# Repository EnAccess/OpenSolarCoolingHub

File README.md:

<div align="center">

# OpenSolarCoolingHub Documentation Index

## 🛡️ License
This project is open source and licensed as follows:
- **Hardware designs** (PCBs, enclosures): [CERN OHL v2.0 - Strongly Reciprocal](https://gitlab.com/ohwr/project/cernohl/-/wikis/uploads/819d71bea3458f71fba6cf4fb0f2de6b/cern_ohl_s_v2.txt)
- **Firmware / Software**: [MIT License](https://opensource.org/license/mit/)
- **Documentation**: [Creative Commons Attribution 4.0 International (CC BY 4.0)](https://creativecommons.org/licenses/by/4.0/)
- See the full [LICENSE](./LICENSE) file for full details.
<br>

**Solar Powered IoT Cooling Hubs**  
_This is a project that brings together architecture, electronics, Internet of Things (IoT), and solar engineering to create affordable and sustainable cooling systems specifically designed for off-grid communities. By integrating smart design with energy-efficient technology and renewable energy sources, the project aims to provide reliable cooling solutions where access to electricity is limited or unavailable. The goal is to improve quality of life, reduce post-harvest losses, and support health and food storage needs in remote or underserved areas._

## 🔗 Cold Room Exterior
This image shows the exterior design of the solar-powered cold room, constructed with durable, insulated materials to maintain optimal internal temperatures. The structure is optimized for energy efficiency and environmental resilience, making it ideal for use in rural or off-grid locations. Its compact and modular design allows for easy transport, installation, and maintenance in remote areas.

## 🔗 IOT Sytem PCB
Displayed here is the custom-designed Printed Circuit Board (PCB) for the IoT system. This board forms the core of the system’s electronics, managing sensor data, control signals, and wireless communication. The PCB is engineered to interface with temperature, humidity, and door sensors, and is optimized for low power consumption and real-time data transmission, supporting remote monitoring and control via a web dashboard.

---

## 🔗 Live IoT Dashboard  
The live IoT dashboard provides real-time monitoring of environmental conditions inside the cold room. It displays key metrics such as temperature, humidity, and system status, allowing users to remotely track and manage performance. The intuitive interface makes it easy for operators to respond to alerts and optimize energy use, ensuring food and medical supplies remain safely stored.

👉 [View Real-time Sensor Display](http://solarcoolingproject.atwebpages.com/RealtimeDisplayImproved.php)

---

<br><br><br><br>

## 📂 Folder-wise Documentation Overview
<br>

## 🧊 1. Cold Room Design 
A comprehensive architectural and systems layout for the off-grid cold room solution. Designed using SolidWorks and Archicad, this section includes construction drawings, 3D models, conceptual diagrams, and thermal/digital integration details.

🔗 Archicad Files - [Link](https://github.com/EnAccess/OpenSolarCoolingHub/tree/b22f68ab80e7eb956e8c33c35e9078b9c4da2ed1/Cold%20Room%20Design/ColdRoom/Archicad%20Files) : Contains the primary architectural plan (FarmFreeze_Munakyalo (ArchiCAD 25).pln) with accompanying documentation.

🔗 CAD Exports - [Link](https://github.com/EnAccess/OpenSolarCoolingHub/tree/b22f68ab80e7eb956e8c33c35e9078b9c4da2ed1/Cold%20Room%20Design/ColdRoom/CAD%20Exports) : Includes PDFs and images of the VIP latrine, tank and base, gate, fence, and full site layout.

🔗 Diagrams - [Link](https://github.com/EnAccess/OpenSolarCoolingHub/tree/b22f68ab80e7eb956e8c33c35e9078b9c4da2ed1/Cold%20Room%20Design/ColdRoom/Diagrams) : Contains structural and conceptual system diagrams.

🔗 System Architecture - [Link](https://github.com/EnAccess/OpenSolarCoolingHub/tree/b22f68ab80e7eb956e8c33c35e9078b9c4da2ed1/Cold%20Room%20Design/SystemArchitecture) : Describes the thermal, electrical, and digital system integration to support off-grid functionality.<br><br>

## 📎 2. Component Datasheets
This folder contains the technical specifications of all key components used across the system. Includes datasheets for sensors (DHT22, MLX90614), power modules, GSM, and Arduino boards. - [Link](https://github.com/EnAccess/OpenSolarCoolingHub/tree/b22f68ab80e7eb956e8c33c35e9078b9c4da2ed1/Component%20Datasheets) 

🔗 readme - [Link](https://github.com/EnAccess/OpenSolarCoolingHub/tree/edee4dc87492873370343514b17ce90f6df560b8/Component%20Datasheets) : Lists and explains each hardware module with links to PDFs.<br><br>

## 💰 3. Financial Model Templates
An Excel-based financial modeling toolkit for evaluating the Pay-as-You-Store pricing strategy and sustainability metrics.
 - [Link](https://github.com/EnAccess/OpenSolarCoolingHub/tree/b22f68ab80e7eb956e8c33c35e9078b9c4da2ed1/Financial%20Model%20Templates) 
🔗 readme.md - [Link](https://github.com/EnAccess/OpenSolarCoolingHub/blob/b22f68ab80e7eb956e8c33c35e9078b9c4da2ed1/Financial%20Model%20Templates/readme.md) : Overview of model usage.

📊 Includes:

Pay_as_You_Store_Financial_Model.xlsx - [Link](https://github.com/EnAccess/OpenSolarCoolingHub/blob/b22f68ab80e7eb956e8c33c35e9078b9c4da2ed1/Financial%20Model%20Templates/Pay_as_You_Store_Financial_Model.xlsx) 

User_Guide_Pay_as_You_Store_Model.pdf - [Link](https://github.com/EnAccess/OpenSolarCoolingHub/blob/b22f68ab80e7eb956e8c33c35e9078b9c4da2ed1/Financial%20Model%20Templates/User_Guide_Pay_as_You_Store_Model.pdf) <br><br>

## 🧠 4. IoT Firmware
Embedded C/C++ code written and compiled using Arduino IDE, designed for the Arduino Mega. This firmware handles sensor input, GSM communication, and relay control logic.

🔗 libraries - [Link](https://github.com/EnAccess/OpenSolarCoolingHub/tree/b22f68ab80e7eb956e8c33c35e9078b9c4da2ed1/IOT%20System%20Arduino%20Firmware/libraries) : Required libraries like DHTlib and Adafruit MLX90614.

🔗 src - [Link](https://github.com/EnAccess/OpenSolarCoolingHub/tree/b22f68ab80e7eb956e8c33c35e9078b9c4da2ed1/IOT%20System%20Arduino%20Firmware/src) : Source code examples including merged sensor tests, GSM modules, relay switching, and address configuration.

🔗 README.md - [Link](https://github.com/EnAccess/OpenSolarCoolingHub/blob/243c3de1c4182eb7e5c24f7d1faaf12b4d0801e8/IOT%20System%20Arduino%20Firmware/README.md) : Firmware overview and setup guide.<br><br>

## 🧱 5. IoT System Enclosure
Designed in OpenSCAD, this section provides both editable 3D models and printable STL files for creating protective enclosures for the PCB.

🔗 3D Models - [Link](https://github.com/EnAccess/OpenSolarCoolingHub/tree/b22f68ab80e7eb956e8c33c35e9078b9c4da2ed1/IOT%20System%20Enclosure/3D%20Models) : .step files for customization and mechanical fitting.

🔗 STL Files - [Link](https://github.com/EnAccess/OpenSolarCoolingHub/tree/b22f68ab80e7eb956e8c33c35e9078b9c4da2ed1/IOT%20System%20Enclosure/STL%20Files) : Ready-to-print STL files for 3D printing.<br><br>

## 💻 6. IoT PCB Design
PCB schematics, layout, and manufacturing-ready files created using CircuitMaker (Altium's free tool). Includes Gerbers, BoMs, pick-and-place files, and fabrication data. - [Link](https://github.com/EnAccess/OpenSolarCoolingHub/tree/b22f68ab80e7eb956e8c33c35e9078b9c4da2ed1/IOT%20System%20PCB) 

🔗 Export Files - [Link](https://github.com/EnAccess/OpenSolarCoolingHub/tree/b22f68ab80e7eb956e8c33c35e9078b9c4da2ed1/IOT%20System%20PCB/Export%20FIles) : Contains all files for fabrication, drilling, and assembly.

🔗 schematics - [Link](https://github.com/EnAccess/OpenSolarCoolingHub/tree/b22f68ab80e7eb956e8c33c35e9078b9c4da2ed1/IOT%20System%20PCB/schematics) : Design files including SchDoc, CMPcbDoc, and the project structure.<br><br>

## 🧪 7. IoT Simulation
Logic simulation and virtual validation of the IoT system using Proteus Professional. - [Link](https://github.com/EnAccess/OpenSolarCoolingHub/tree/2582ba2290185b933453911665ca5a5f1b0d1c63/IOT%20System%20Simulation%20with%20Proteus%20Pro) 

🔗 readmefile.md - [Link](https://github.com/EnAccess/OpenSolarCoolingHub/blob/2582ba2290185b933453911665ca5a5f1b0d1c63/IOT%20System%20Simulation%20with%20Proteus%20Pro/readmefile.md) : Instructions and configuration.

Includes:

Cold Solar Storage Proteus Simulation.pdsprj<br><br>

## 🌐 8. IoT System Website
Built with PHP, MySQL, HTML, CSS, the cloud dashboard enables real-time monitoring of cold room conditions remotely.

🔗 public - [Link](https://github.com/EnAccess/OpenSolarCoolingHub/tree/2582ba2290185b933453911665ca5a5f1b0d1c63/IOT%20System%20Website/public) : All PHP scripts for inserting, fetching, and displaying sensor data.<br><br>
🔗 readmefile.md - [Link](https://github.com/EnAccess/OpenSolarCoolingHub/blob/2582ba2290185b933453911665ca5a5f1b0d1c63/IOT%20System%20Website/README.md)

## 🎥 9. Project Images and Videos
A visual gallery showing the project progress and deliverables including 3D PCB renderings and schematics.
 - [Link](https://github.com/EnAccess/OpenSolarCoolingHub/tree/2582ba2290185b933453911665ca5a5f1b0d1c63/Project%20Images%20and%20Videos) 

Includes: PCB 2D.PNG, PCB 3D ANGLE.PNG, Schematic.PNG, etc.<br><br>

## 🧪 10. System Testing
This section documents the calibration, test planning, and final performance results of the overall system.

🔗 Calibration - [Link](https://github.com/EnAccess/OpenSolarCoolingHub/tree/2582ba2290185b933453911665ca5a5f1b0d1c63/System%20Testing/Calibration) : Logs and notes on sensor tuning.

🔗 TestPlans - [Link](https://github.com/EnAccess/OpenSolarCoolingHub/tree/2582ba2290185b933453911665ca5a5f1b0d1c63/System%20Testing/TestPlans) : Structured validation plans.

🔗 TestResults - [Link](https://github.com/EnAccess/OpenSolarCoolingHub/tree/2582ba2290185b933453911665ca5a5f1b0d1c63/System%20Testing/TestResults) : Performance outcomes and notes.<br><br>

## 📚 11. Technical References
Academic and industry references used for component selection, system design, and technical justification.
 - [Link](https://github.com/EnAccess/OpenSolarCoolingHub/tree/2582ba2290185b933453911665ca5a5f1b0d1c63/Technical%20References) 
<br><br>

## 📘 12. User Manual
End-user guide for setup, usage, and maintenance of the cold room system.
 - [Link](https://github.com/EnAccess/OpenSolarCoolingHub/tree/2582ba2290185b933453911665ca5a5f1b0d1c63/User%20Manual) 
🔗 readme.md - [Link](https://github.com/EnAccess/OpenSolarCoolingHub/blob/2582ba2290185b933453911665ca5a5f1b0d1c63/User%20Manual/readme.md) : Step-by-step instructions for installation and safe use. <br><br>

---

</div>

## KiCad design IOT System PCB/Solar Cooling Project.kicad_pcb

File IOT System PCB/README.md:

# IoT System PCB – Open Solar Cooling Hub using KiCAD

This repository contains the PCB design files for the IoT Monitoring System used in the Open Solar Cooling Hub, created and managed using **KiCAD**. The project includes schematics, PCB layout, fabrication files (Gerbers, drill files), assembly files (BOM, Pick & Place), and a 3D model for enclosure design. This guide explains how to open, modify, and produce the PCB using KiCAD.

---

## Prerequisites

1. **Install KiCAD**:
   - Download KiCAD 9.0.3 from [kicad.org](https://www.kicad.org/download/) for Windows, macOS, or Linux.
   - Install and launch KiCAD.
  
   - Application: KiCad x64 on x64

   - Libraries:
     	- wxWidgets 3.2.8
      - FreeType 2.13.3
      - HarfBuzz 10.2.0
      - FontConfig 2.15.0
      - libcurl/8.13.0-DEV Schannel zlib/1.3.1

2. **Required Files**:
   - `Solar Cooling Project.kicad_pro`: KiCAD project file.
   - `Solar Cooling Project.kicad_sch`: Schematic file.
   - `Solar Cooling Project.kicad_pcb`: PCB layout file.
   - Reference files :
     - Gerber files (`Solar Cooling Project-F_Cu.gbr`, `B_Cu.gbr`, etc.)
     - Drill files (`Solar Cooling Project-PTH.drl`, `NPTH.drl`)
     - BOM (`BOM_PartType-Open Solar Cooling Hub PCB Project.xlsx`)
     - Pick & Place (`Pick Place for IOT B oard FIle.txt`)
     - Assembly PDF (`Assembly.PDF`)
     - 3D model (`IOT B oard FIle.step`)

---

## Folder Structure and Content Description

The project follows standard hardware development practices, with files organized for PCB fabrication, assembly, and modification.

| Folder/File | Purpose |
|-------------|---------|
| `Gerber/` | PCB fabrication layers (copper, soldermask, silkscreen, etc.) |
| `NC Drill/` | Drill files for PTH and NPTH holes |
| `PCBA/` | Assembly files (BOM, Pick & Place, Assembly PDF) |
| `ExportSTEP/` | 3D STEP model for enclosure design |
| `Solar Cooling Project.kicad_pro` | KiCAD project file |
| `Solar Cooling Project.kicad_sch` | Schematic file |
| `Solar Cooling Project.kicad_pcb` | PCB layout file |
| `README.md` | Project documentation |

---

## How to Open and Modify the PCB Design in KiCAD

### 1. Open the Project
1. Launch KiCAD and open `Solar Cooling Project.kicad_pro` in the project manager.
2. This loads the schematic (`Solar Cooling Project.kicad_sch`) and PCB layout (`Solar Cooling Project.kicad_pcb`).

### 2. Edit the Schematic
1. Open the schematic editor (Eeschema) by clicking the schematic icon in the project manager.
2. Verify components, connections, and net labels against the original BOM and schematic reference .
3. **Modify **:
   - Add/remove components using KiCAD’s symbol libraries or create custom symbols.
   - Update net labels for clarity.
   - Assign footprints to each symbol via the “Assign Footprints” tool, ensuring compatibility with the BOM and Pick & Place file.
4. Generate a netlist (File > Export > Netlist) for PCB layout.

### 3. Edit the PCB Layout
1. Open the PCB editor (Pcbnew) by clicking the PCB icon in the project manager.
2. Import the netlist (File > Import > Netlist) to populate components.
3. **Validate Layout**:
   - Compare the board outline with `Solar Cooling Project-Edge_Cuts.gbr`.
   - Verify component placements using `Pick Place for IOT B oard FIle.txt` (import via File > Import > Placement File).
   - Check routing against Gerber files (`F_Cu.gbr`, `B_Cu.gbr`) using KiCAD’s Gerber Viewer (File > Import > Gerber Files).
4. **Modify (if needed)**:
   - Adjust component positions in Pcbnew.
   - Reroute traces to optimize the layout.
   - Update the board outline on the `Edge.Cuts` layer.
5. **Import Drill Files**:
   - Import `Solar Cooling Project-PTH.drl` and `NPTH.drl` (File > Import > Drill Files) to ensure correct via and hole placement.
6. **3D Verification**:
   - View the PCB in 3D (View > 3D Viewer) and compare with `IOT B oard FIle.step`.
   - Assign 3D models to footprints if needed (Footprint Properties > 3D Settings).

### 4. Generate Fabrication and Assembly Files
1. **Gerber Files**:
   - In Pcbnew, go to File > Plot.
   - Select layers: `F.Cu`, `B.Cu`, `F.Silkscreen`, `B.Silkscreen`, `F.Mask`, `B.Mask`, `Edge.Cuts`.
   - Output to a `Gerber/` folder.
   - Verify against original Gerbers using a Gerber viewer (e.g., KiCAD’s Gerber Viewer or Gerbv).
2. **Drill Files**:
   - In Pcbnew, go to File > Fabrication Outputs > Drill Files.
   - Generate Excellon drill files for PTH and NPTH.
   - Output to a `NC Drill/` folder.
3. **Bill of Materials (BOM)**:
   - In Eeschema, go to Tools > Generate Bill of Materials.
   - Export as CSV or XLSX to `PCBA/BOM.xlsx`.
   - Cross-check with `BOM_PartType-Open Solar Cooling Hub PCB Project.xlsx`.
4. **Pick & Place File**:
   - In Pcbnew, go to File > Fabrication Outputs > Component Placement File.
   - Output to `PCBA/Pick_Place.txt`.
   - Verify against `Pick Place for IOT B oard FIle.txt`.
5. **Assembly Drawing**:
   - In Pcbnew, go to File > Plot and export a PDF of the board layout to `PCBA/Assembly.pdf`.
6. **3D Model**:
   - In Pcbnew, go to File > Export > STEP.
   - Save to `ExportSTEP/Solar_Cooling_Project.step`.

### 5. Validate Outputs
- **Gerber Comparison**: Use a Gerber viewer to ensure KiCAD-generated Gerbers match the original Gerbers.
- **BOM and Pick & Place**: Confirm component lists and placements align with the original files.
- **Fabrication Test**: Send Gerber and drill files to a PCB manufacturer (e.g., JLCPCB) to verify acceptance.
- **Assembly Check**: Provide BOM, Pick & Place, and Assembly PDF to an SMT service for validation.

---

## How to Use the Outputs

- **Fabrication**: Send the `Gerber/` and `NC Drill/` folders to a PCB manufacturer e.g., JLCPCB, PCBWay.
- **Assembly**: Provide `PCBA/BOM.xlsx`, `PCBA/Pick_Place.txt`, and `PCBA/Assembly.pdf` to an SMT assembly service.
- **Modify/Rebuild**: Use `Solar Cooling Project.kicad_sch` and `.kicad_pcb` in KiCAD to edit the design and regenerate outputs.
- **Enclosure Design**: Use `ExportSTEP/Solar_Cooling_Project.step` in CAD tools like OpenSCAD or FreeCAD.

---

## Licensing

This project is licensed under the **CERN Open Hardware License v2.0**. Ensure all modifications and derivatives retain this license.

---

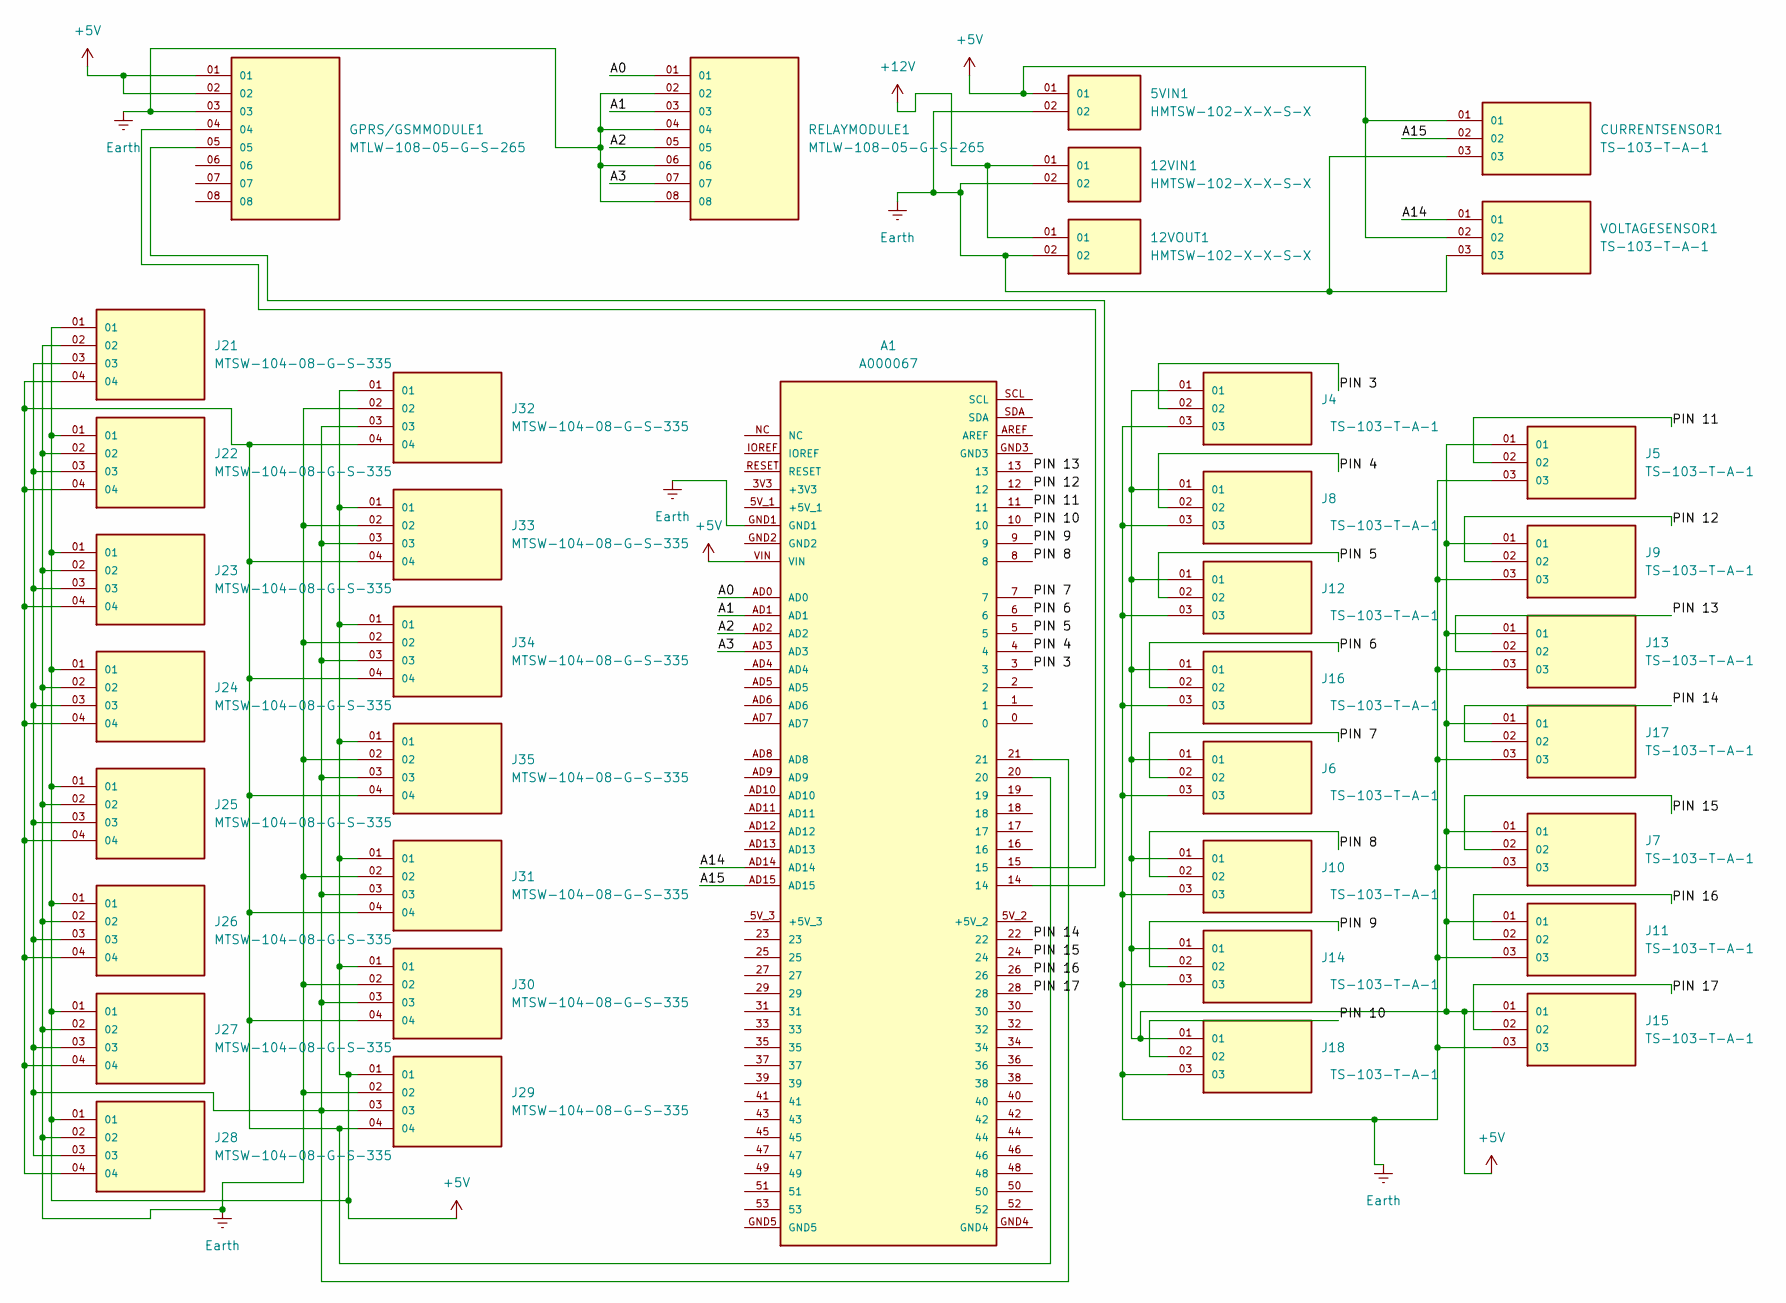
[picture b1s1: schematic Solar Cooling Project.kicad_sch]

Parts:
5VIN1, 12VIN1, 12VOUT1: HMTSW-102-X-X-S-X; SAMTEC_HMTSW-102-X-X-S-X; PARTREV A
A1: A000067; MODULE_A000067; PARTREV 3
CURRENTSENSOR1: TS-103-T-A-1; SAMTEC_TS-103-T-A-1; PARTREV R
GPRS/GSMMODULE1: MTLW-108-05-G-S-265; SAMTEC_MTLW-108-05-G-S-265; PARTREV R
J4, J5, J6, J7, J8, J9, J10, J11, J12, J13, J14, J15, J16, J17, J18: TS-103-T-A-1; SAMTEC_TS-103-T-A-1; PARTREV R
J21, J22, J23, J24, J25, J26, J27, J28, J29, J30, J31, J32, J33, J34, J35: MTSW-104-08-G-S-335; SAMTEC_MTSW-104-08-G-S-335; PARTREV R
RELAYMODULE1: MTLW-108-05-G-S-265; SAMTEC_MTLW-108-05-G-S-265; PARTREV R
VOLTAGESENSOR1: TS-103-T-A-1; SAMTEC_TS-103-T-A-1; PARTREV R

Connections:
+5V: 5VIN1.01, A1.VIN, CURRENTSENSOR1.01, GPRS/GSMMODULE1.01, GPRS/GSMMODULE1.02, J4.01, J5.01, J6.01, J7.01, J8.01, J9.01, J10.01, J11.01, J12.01, J13.01, J14.01, J15.01, J16.01, J17.01, J18.01, J21.01, J22.01, J23.01, J24.01, J25.01, J26.01, J27.01, J28.01, J29.01, J30.01, J31.01, J32.01, J33.01, J34.01, J35.01, VOLTAGESENSOR1.02
+12V: 12VIN1.01, 12VOUT1.01
/A0: A1.AD0, RELAYMODULE1.01
/A1: A1.AD1, RELAYMODULE1.03
/A2: A1.AD2, RELAYMODULE1.05
/A3: A1.AD3, RELAYMODULE1.07
/A14: A1.AD14, VOLTAGESENSOR1.01
/A15: A1.AD15, CURRENTSENSOR1.02
/PIN 3: A1.3, J4.02
/PIN 4: A1.4, J8.02
/PIN 5: A1.5, J12.02
/PIN 6: A1.6, J16.02
/PIN 7: A1.7, J6.02
/PIN 8: A1.8, J10.02
/PIN 9: A1.9, J14.02
/PIN 10: A1.10, J18.02
/PIN 11: A1.11, J5.02
/PIN 12: A1.12, J9.02
/PIN 13: A1.13, J13.02
/PIN 14: A1.22, J17.02
/PIN 15: A1.24, J7.02
/PIN 16: A1.26, J11.02
/PIN 17: A1.28, J15.02
Earth: 5VIN1.02, 12VIN1.02, 12VOUT1.02, A1.GND1, CURRENTSENSOR1.03, GPRS/GSMMODULE1.03, J4.03, J5.03, J6.03, J7.03, J8.03, J9.03, J10.03, J11.03, J12.03, J13.03, J14.03, J15.03, J16.03, J17.03, J18.03, J21.02, J22.02, J23.02, J24.02, J25.02, J26.02, J27.02, J28.02, J29.02, J30.02, J31.02, J32.02, J33.02, J34.02, J35.02, RELAYMODULE1.02, RELAYMODULE1.04, RELAYMODULE1.06, RELAYMODULE1.08, VOLTAGESENSOR1.03
unnamed: A1.14, GPRS/GSMMODULE1.05
unnamed: A1.15, GPRS/GSMMODULE1.04
unnamed: A1.20, J21.04, J22.04, J23.04, J24.04, J25.04, J26.04, J27.04, J28.04, J29.04, J30.04, J31.04, J32.04, J33.04, J34.04, J35.04
unnamed: A1.21, J21.03, J22.03, J23.03, J24.03, J25.03, J26.03, J27.03, J28.03, J29.03, J30.03, J31.03, J32.03, J33.03, J34.03, J35.03

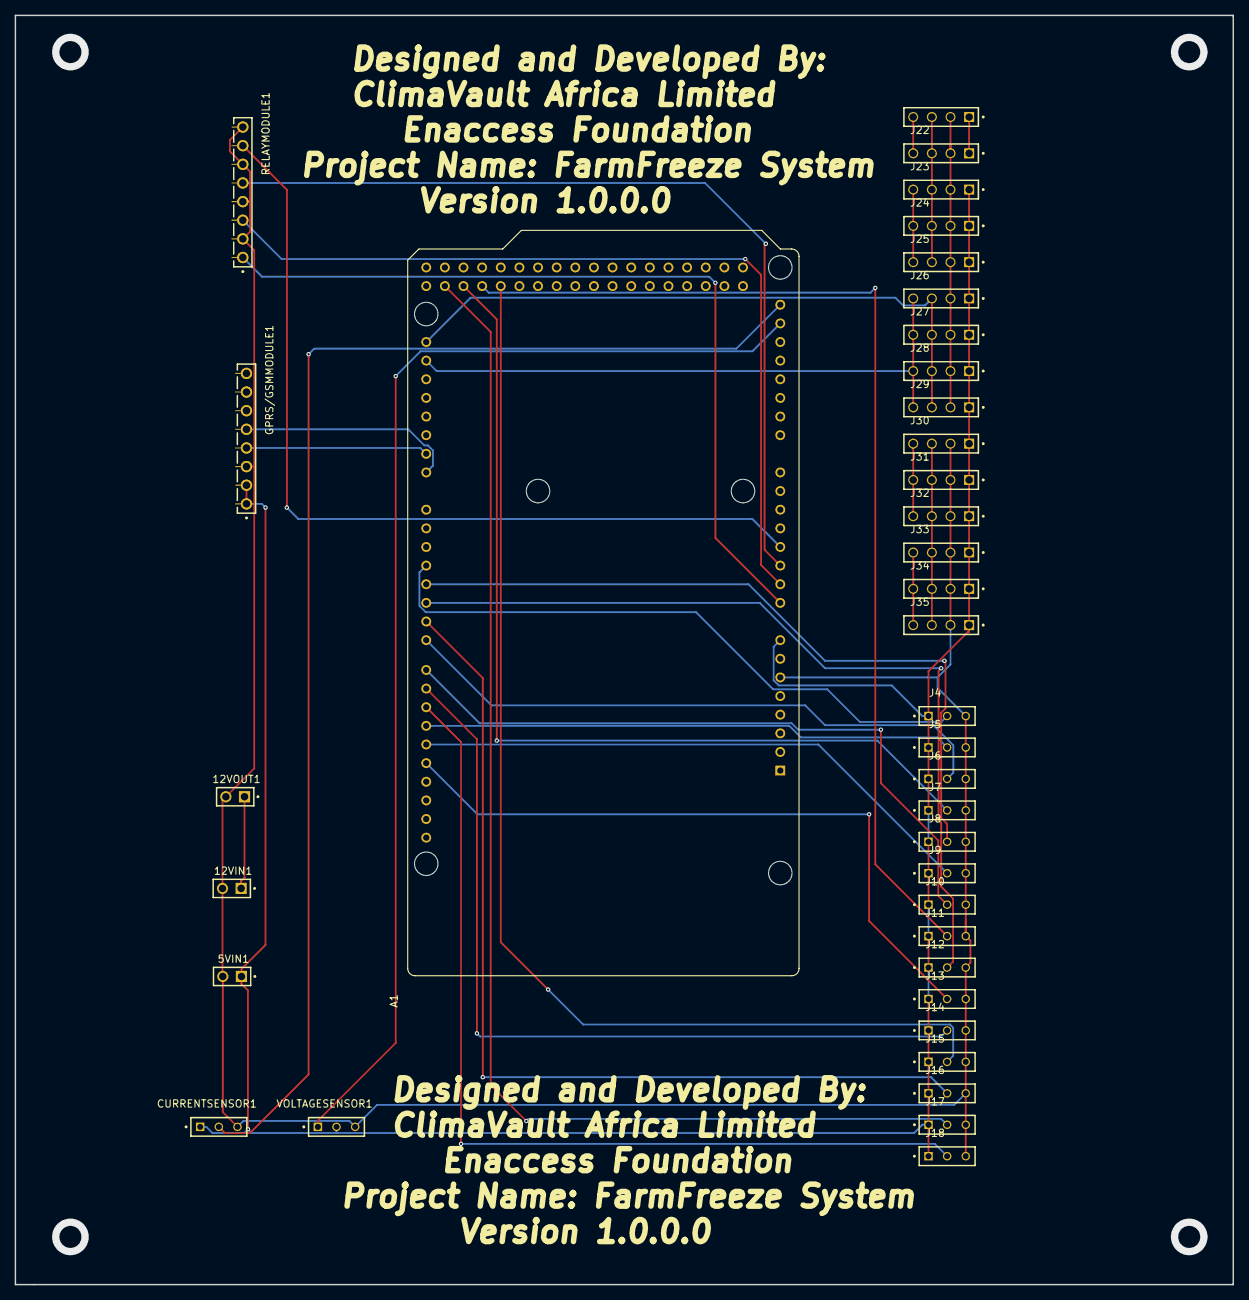
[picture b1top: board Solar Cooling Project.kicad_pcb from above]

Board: 2 copper layers, 166.0 x 173.0 mm, 38 parts (0 on the bottom side), 28 nets.

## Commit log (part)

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2025-04-15 Add `.github/PULL_REQUEST_TEMPLATE.md`
2025-04-15 Add `.github/ISSUE_TEMPLATE/config.yml`
2025-04-15 Add `.github/ISSUE_TEMPLATE/feature_request.yml`
2025-04-15 Add `CODE_OF_CONDUCT.md`
2025-04-15 Add `.github/ISSUE_TEMPLATE/bug_report.yml`
2025-04-15 Add `.github/SECURITY.md`
2025-04-15 Add `CONTRIBUTING.md`
2025-04-15 Add boilderplate
2025-04-15 Fix lint
2025-04-15 Markdown Lint
2025-04-15 Add boilderplate (#1)
    * Add boilderplate
    * Fix lint
    * Markdown Lint
2025-04-15 Add Github Pages release flow
2025-04-15 Add Github Pages release flow (#2)
2025-04-15 Fix Github pages
2025-04-22 Update README.md (#3)updated code
    added accounts
2025-04-22 Update markdown-examples.md
    added modificatio
2025-04-22 Update markdown-examples.md (#4)
    added modificatio
2025-04-24 Create Bashirtestfile.txt
    iam creating to put the code there
2025-04-24 Create Bashirtestfile.txt (#5)
    iam creating to put the code there
2025-04-24 Add files via upload
    i aqm done desihning the roof
2025-04-24 Uploading files
    i am done designing the roof
2025-04-28 Add `DISCORD_ETIQUETTE.md`
2025-04-28 Create testfile
2025-04-28 Rename testfile to testfile
2025-04-28 Create Meeting Notes
2025-04-28 Update Meeting Notes
2025-04-28 Create ReadMe.md (#7)
2025-05-05 Create IOT System Simulation with Proteus
2025-05-05 Add files via upload
    I2C Scanner code for checking the i2c address of each temperature sensor before and after changing it
2025-05-05 Update Meeting Notes (#8)
2025-05-05 Temperature Sensor Test code
    Temperature Sensor Test code
2025-05-05 Code to Change address for each temperature sensor
    Code to Change address for each temperature sensor
2025-05-05 DHT22 Temperature sensor code
    DHT22 Temperature sensor code
2025-05-05 Humidity sensor test code and hex files for proteus professional
2025-05-05 Create readmefile.md (#14)
2025-05-05 Proteus Basic Simulation
    Proteus Basic Simulation
2025-05-19 Humidity sensor test code and hex files for proteus professional (#13)
2025-05-19 DHT22 Temperature sensor code (#12)
    DHT22 Temperature sensor code
2025-05-19 Code to Change address for each temperature sensor (#11)
    Code to Change address for each temperature sensor
2025-05-20 Temperature Sensor Test code (#10)
    Temperature Sensor Test code
2025-05-20 Add files via upload (#9)
    I2C Scanner code for checking the i2c address of each temperature sensor before and after changing it
2025-05-25 Add files via upload
    Relay Module Testing, 10 humidity Sensors and 10 Temperature sensors and relay module merged, GSMS Module Test.
2025-05-27 Add files via upload (#15)
    Relay Module Testing, 10 humidity Sensors and 10 Temperature sensors and relay module merged, GSMS Module Test.
2025-05-27 Create readme.md (#16)
2025-05-27 Update readme.md (#17)
2025-06-03 An ArchiCAD file of the design (version 25)
2025-06-11 Add files via upload
    Working Code will Temperature, Humidity and Remote Monitoring
2025-06-11 Add files via upload
    Website Basic PHP FIles
2025-06-11 Add files via upload
    MySQL Database Structure
2025-06-13 Add files via upload (#20)
    MySQL Database Structure
2025-06-13 Add files via upload (#19)
    Website Basic PHP FIles
2025-06-13 Add files via upload (#18)
    Working Code will Temperature, Humidity and Remote Monitoring
2025-06-29 Add files via upload (#21)
2025-06-30 Add files via upload
    FInal Working Code
2025-06-30 Cold Room Design
2025-07-24 Update `readme.md`
2025-07-31 Create LICENSE
2025-09-04 Add files via upload
    Bill of material
2025-09-09 Add files via upload
    CAD Exports PDF version
2025-09-09 Create FreeCAD Files
    This folder has the version of the designs in FreeCAD
2025-09-09 Create 3D Files
